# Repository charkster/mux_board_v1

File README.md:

# mux_board_v1
Custom PCB with ItsyBitsy M0 Express controlling **FOUR ADG1606BRUZ 16 input muxes!**

**--> UPDATED design available: [mux_board_v5](https://github.com/charkster/mux_board_v5) <--**

Check-out my **PDF** [schematic](https://github.com/charkster/mux_board_v1/blob/main/kicad/mux_board_v1_sch_plot.pdf) !!

This board is super-easy to order from Oshpark. Just upload kicad/mux_board_v1.kicad_pcb and pay $31 for 3 boards (including shipping).
The ItsyBitsy M0 Express board was selected as (1) I am very familar with the samd21, (2) it has enought gpios to control all the muxes and (3) it is $12 and almost always in-stock. The ItsyBitsy board can be programmed by just double-clicking the reset button and drag-n-drop the itsybitsy_m0-usbtmc_mux_board.uf2 file.

**Welcome to the fricken future people...** drag-n-drop the kicad_pcb file to order the board, and drag-n-drop the uf2 file to program the MCU! Sorry, nothing I can do about the soldering.

Mux outputs are on the 1757268 connector, which is a Phoenix Contact connector. This connector can be omitted and posts can be put in the holes.

Dual channel opamp and muxes working great, but the level-shifter schematic is incorrect (don't populate the NVT2008 part). The NVT2008 needs to have high value resistors connect to the VREFB and EN inputs (unlike the TI TXS01018E).

What am I planning to do with this board? I need to connect two Keithley 2460 SMUs to my ASIC board to support bench trimming. I thought this would be a cool new lab instrument. The VDD PIN can be driven by the USB's 5V or externally up to 16V (mux inputs should be less than VDD).

Here are the SCPI commands which can be used:

**MUX1:EN 1** # enable MUX1, a zero will disable the mux

**MUX1:SEL 1** # select S1 input, values 1 through 16 are valid

**MUX1:EN?** # this query returns the state of MUX1

**MUX1:SEL?** # this query returns the presently selected input

**SOURC1:VOLT:LEV 2.2** # drive 2.2V from DAC

**SOURC1:VOLT:LEV?** # this query returns the DAC level

***RST** # disables all MUX enables and sets DAC to 0V

***IDN?** # returns valid commands and this URL

The tinyusb_usbtmc files are modifications of https://github.com/hathach/tinyusb source files.

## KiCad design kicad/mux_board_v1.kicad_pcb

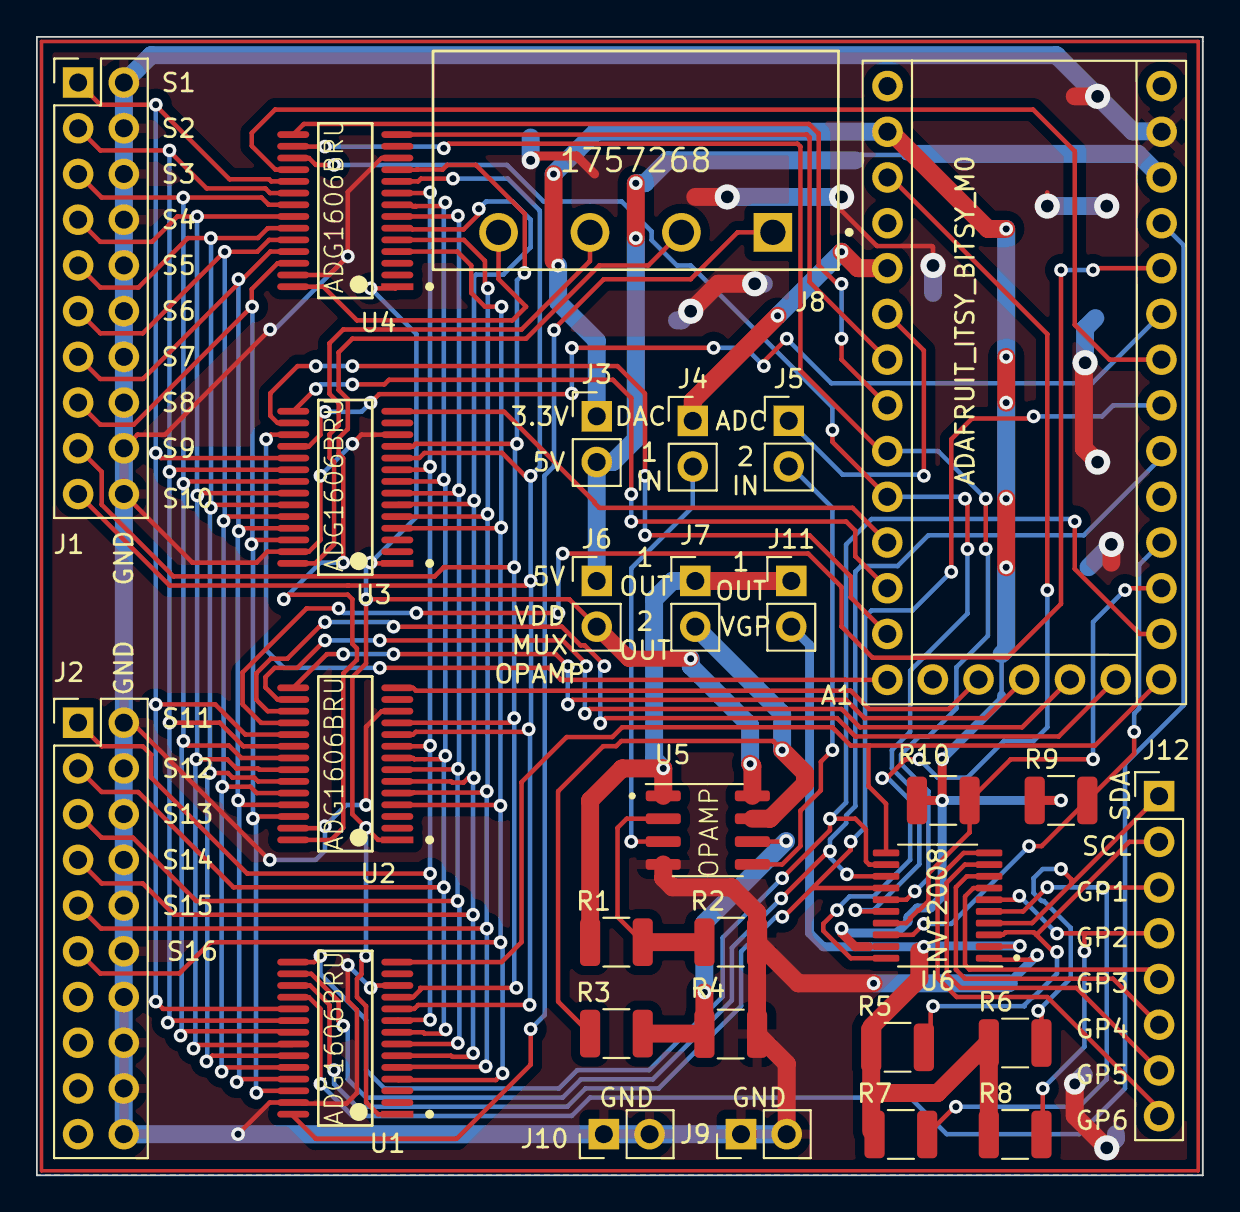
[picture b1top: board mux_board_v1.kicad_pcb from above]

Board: 2 copper layers, 64.8 x 63.2 mm, 29 parts (0 on the bottom side), 64 nets.

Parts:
A1: ADAFRUIT_ITSY_BITSY_M0; Adafruit_Itsy_Bitsy_M0
J1, J2: Conn_02x10_Odd_Even; PinHeader_2x10_P2.54mm_Vertical
J3, J4, J5, J6, J7, J9, J10, J11: Conn_01x02_Male; PinHeader_1x02_P2.54mm_Vertical
J8: 1757268; Phoenix_Contact-1757268-0
J12: Conn_01x08_Male; PinHeader_1x08_P2.54mm_Vertical
R1, R3: 10k; R_1210_3225Metric
R2, R4: 5k; R_1210_3225Metric
R5, R6, R7, R8, R9, R10: 1k; R_1210_3225Metric
U1, U2, U3, U4: ADG1606BRU; Analog_Devices-RU-28-0-0-IPC_A
U5: OPAMP; SOIC-8-1EP_3.9x4.9mm_P1.27mm_EP2.29x3mm
U6: NVT2008; TSSOP-20_4.4x6.5mm_P0.65mm

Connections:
+3V3: A1.32 (3V3), J3.1, R9.1, R10.1, U6.19 (VREFB)
+5V: A1.3 (VUSB), J3.2, J6.1
/1IN-: R1.2, R2.1, U5.2 (1IN-)
/1OUT: J7.1, J11.1, R1.1, U5.1 (1OUT)
/2OUT: J7.2, R3.1, U5.7 (2OUT)
/ADC: A1.28 (A1), J5.1
/DAC: A1.29 (A0), J4.1
/GPIO1: J12.3, R7.2, U6.5 (A3)
/GPIO2: J12.4, R8.2, U6.6 (A4)
/GPIO3: J12.5, U6.7 (A5)
/GPIO4: J12.6, U6.8 (A6)
/GPIO5: J12.7, U6.9 (A7)
/GPIO6: J12.8, U6.10 (A8)
/LS_EN: A1.31 (AVREF), U6.20 (EN)
/MUX1_EN: A1.4 (D13), U1.18 (EN)
/MUX1_OUT: J8.1, U1.28 (D)
/MUX1_SEL0: A1.8 (D9), U1.17 (A0), U6.14 (B5)
/MUX1_SEL1: A1.9 (D7), U1.16 (A1), U6.13 (B6)
/MUX1_SEL2: A1.13 (D1), U1.15 (A2), U6.12 (B7)
/MUX1_SEL3: A1.14 (D0), U1.14 (A3), U6.11 (B8)
/MUX2_EN: A1.5 (D12), U2.18 (EN)
/MUX2_OUT: J8.2, U2.28 (D)
/MUX2_SEL0: A1.15 (D4), U2.17 (A0)
/MUX2_SEL1: A1.16 (D3), U2.16 (A1)
/MUX2_SEL2: A1.17 (SWCLK), U2.15 (A2)
/MUX2_SEL3: A1.18 (SWDIO), U2.14 (A3)
/MUX3_EN: A1.6 (D11), U3.18 (EN)
/MUX3_OUT: J8.3, U3.28 (D)
/MUX3_SEL0: A1.20 (D2), U3.17 (A0)
/MUX3_SEL1: A1.21 (MISO), U3.16 (A1)
/MUX3_SEL2: A1.22 (MOSI), U3.15 (A2)
/MUX3_SEL3: A1.23 (SCK), U3.14 (A3)
/MUX4_EN: A1.7 (D10), U4.18 (EN)
/MUX4_OUT: J8.4, U4.28 (D)
/MUX4_SEL0: A1.24 (A5), U4.17 (A0), U6.16 (B3)
/MUX4_SEL1: A1.25 (A4), U4.16 (A1), U6.15 (B4)
/MUX4_SEL2: A1.26 (A3), U4.15 (A2)
/MUX4_SEL3: A1.27 (A2), U4.14 (A3)
/S1: J1.1, U1.19 (S1), U2.19 (S1), U3.19 (S1), U4.19 (S1)
/S2: J1.3, U1.20 (S2), U2.20 (S2), U3.20 (S2), U4.20 (S2)
/S3: J1.5, U1.21 (S3), U2.21 (S3), U3.21 (S3), U4.21 (S3)
/S4: J1.7, U1.22 (S4), U2.22 (S4), U3.22 (S4), U4.22 (S4)
/S5: J1.9, U1.23 (S5), U2.23 (S5), U3.23 (S5), U4.23 (S5)
/S6: J1.11, U1.24 (S6), U2.24 (S6), U3.24 (S6), U4.24 (S6)
/S7: J1.13, U1.25 (S7), U2.25 (S7), U3.25 (S7), U4.25 (S7)
/S8: J1.15, U1.26 (S8), U2.26 (S8), U3.26 (S8), U4.26 (S8)
/S9: J1.17, U1.11 (S9), U2.11 (S9), U3.11 (S9), U4.11 (S9)
/S10: J1.19, U1.10 (S10), U2.10 (S10), U3.10 (S10), U4.10 (S10)
/S11: J2.1, U1.9 (S11), U2.9 (S11), U3.9 (S11), U4.9 (S11)
/S12: J2.3, U1.8 (S12), U2.8 (S12), U3.8 (S12), U4.8 (S12)
/S13: J2.5, U1.7 (S13), U2.7 (S13), U3.7 (S13), U4.7 (S13)
/S14: J2.7, U1.6 (S14), U2.6 (S14), U3.6 (S14), U4.6 (S14)
/S15: J2.9, U1.5 (S15), U2.5 (S15), U3.5 (S15), U4.5 (S15)
/S16: J2.11, U1.4 (S16), U2.4 (S16), U3.4 (S16), U4.4 (S16)
/SCL: J12.2, R5.2, U6.3 (A1)
/SCL_3V3: A1.11 (SCL), R9.2, U6.18 (B1)
/SDA: J12.1, R6.2, U6.4 (A2)
/SDA_3V3: A1.12 (SDA), R10.2, U6.17 (B2)
/VDD: J6.2, U1.1 (VDD), U2.1 (VDD), U3.1 (VDD), U4.1 (VDD), U5.8 (VDD)
/VREFA: J11.2, R5.1, R6.1, R7.1, R8.1, U6.2 (VREFA)
GND: A1.2 (GND), J1.2, J1.4, J1.6, J1.8, J1.10, J1.12, J1.14, J1.16, J1.18, J1.20, J2.2, J2.4, J2.6, J2.8, J2.10, J2.12, J2.14, J2.16, J2.18, J2.20, J9.1, J9.2, J10.1, J10.2, R2.2, R4.2, U1.12 (GND), U1.27 (VSS), U2.12 (GND), U2.27 (VSS), U3.12 (GND), U3.27 (VSS), U4.12 (GND), U4.27 (VSS), U5.4 (GND), U6.1 (GND)
unnamed: J4.2, U5.3 (1IN+)
unnamed: J5.2, U5.5 (2IN+)
unnamed: R3.2, R4.1, U5.6 (2IN-)

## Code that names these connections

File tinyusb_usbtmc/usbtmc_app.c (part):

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#define DOTSTAR_CLK     PORT_PA00
#define DAC_PORT        PORT_PA02
#define ADC_PORT        PORT_PB08 // PORT B
#define MUX1_EN_PORT    PORT_PA17
#define MUX1_EN_PIN      PIN_PA17
#define MUX1_S0_PORT    PORT_PA07
#define MUX1_S0_PIN      PIN_PA07
#define MUX1_S1_PORT    PORT_PA21
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#define MUX1_S2_PIN      PIN_PA10
#define MUX1_S3_PORT    PORT_PA11
#define MUX1_S3_PIN      PIN_PA11
#define MUX2_EN_PORT    PORT_PA19
#define MUX2_EN_PIN      PIN_PA19
#define MUX2_S0_PORT    PORT_PA08
#define MUX2_S0_PIN      PIN_PA08
#define MUX2_S1_PORT    PORT_PA09
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#define MUX2_S2_PIN      PIN_PA30
#define MUX2_S3_PORT    PORT_PA31
#define MUX2_S3_PIN      PIN_PA31
#define MUX3_EN_PORT    PORT_PA16
#define MUX3_EN_PIN      PIN_PA16
#define MUX3_S0_PORT    PORT_PA14
#define MUX3_S0_PIN      PIN_PA14
#define MUX3_S1_PORT    PORT_PA12
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#define MUX3_S2_PIN      PIN_PB10
#define MUX3_S3_PORT    PORT_PB11 // PORT B
#define MUX3_S3_PIN      PIN_PB11
#define MUX4_EN_PORT    PORT_PA18
#define MUX4_EN_PIN      PIN_PA18
#define MUX4_S0_PORT    PORT_PB02 // PORT B
#define MUX4_S0_PIN      PIN_PB02
#define MUX4_S1_PORT    PORT_PA05
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#define MUX4_S2_PIN      PIN_PA04
#define MUX4_S3_PORT    PORT_PB09 // PORT B
#define MUX4_S3_PIN      PIN_PB09
#define LS_EN_PORT      PORT_PA03
#define LS_EN_PIN        PIN_PA03
#define GPIO1_PORT      PORT_PB02 // PORT B, same as MUX4_S0_PORT
#define GPIO1_PIN        PIN_PB02
#define GPIO2_PORT      PORT_PA05 //         same as MUX4_S1_PORT
#define GPIO2_PIN        PIN_PA05
#define GPIO3_PORT      PORT_PA04 //         same as MUX4_S2_PORT
#define GPIO3_PIN        PIN_PA04
#define GPIO4_PORT      PORT_PB09 // PORT B, same as MUX4_S3_PORT
#define GPIO4_PIN        PIN_PB09
#define GPIO5_PORT      PORT_PA14 //         same as MUX3_S0_PORT
#define GPIO5_PIN        PIN_PA14
#define GPIO6_PORT      PORT_PA12 //         same as MUX3_S1_PORT
#define GPIO6_PIN        PIN_PA12
#define SDA_PORT        PORT_PA22
#define SCL_PORT        PORT_PB11  // PORT B
#define DAC_MAX_VALUE   1024 // 10bit value
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#define MUX4_SEL_QUERY  "mux4:sel?"        // MUX4:SEL
#define MUX4_EN_CMD     "mux4:en "         // MUX4:ENable
#define MUX4_EN_QUERY   "mux4:en?"         // MUX4:ENable
#define GPIO1_LEV_CMD    "gpio1:lev "      // GPIO1:LEVel
#define GPIO1_LEV_QUERY  "gpio1:lev?"      // GPIO1:LEVel
#define GPIO1_DIR_CMD    "gpio1:dir "      // GPIO1:DIRection
#define GPIO1_DIR_QUERY  "gpio1:dir?"      // GPIO1:DIRection
#define GPIO2_LEV_CMD    "gpio2:lev "      // GPIO2:LEVel
#define GPIO2_LEV_QUERY  "gpio2:lev?"      // GPIO2:LEVel
#define GPIO2_DIR_CMD    "gpio2:dir "      // GPIO2:DIRection
#define GPIO2_DIR_QUERY  "gpio2:dir?"      // GPIO2:DIRection
#define GPIO3_LEV_CMD    "gpio3:lev "      // GPIO3:LEVel
#define GPIO3_LEV_QUERY  "gpio3:lev?"      // GPIO3:LEVel
#define GPIO3_DIR_CMD    "gpio3:dir "      // GPIO3:DIRection
#define GPIO3_DIR_QUERY  "gpio3:dir?"      // GPIO3:DIRection
#define GPIO4_LEV_CMD    "gpio4:lev "      // GPIO4:LEVel
#define GPIO4_LEV_QUERY  "gpio4:lev?"      // GPIO4:LEVel
#define GPIO4_DIR_CMD    "gpio4:dir "      // GPIO4:DIRection
#define GPIO4_DIR_QUERY  "gpio4:dir?"      // GPIO4:DIRection
#define GPIO5_LEV_CMD    "gpio5:lev "      // GPIO5:LEVel
#define GPIO5_LEV_QUERY  "gpio5:lev?"      // GPIO5:LEVel
#define GPIO5_DIR_CMD    "gpio5:dir "      // GPIO5:DIRection
#define GPIO5_DIR_QUERY  "gpio5:dir?"      // GPIO5:DIRection
#define GPIO6_LEV_CMD    "gpio6:lev "      // GPIO6:LEVel
#define GPIO6_LEV_QUERY  "gpio6:lev?"      // GPIO6:LEVel
#define GPIO6_DIR_CMD    "gpio6:dir "      // GPIO6:DIRection
#define GPIO6_DIR_QUERY  "gpio6:dir?"      // GPIO6:DIRection
#define END_RESPONSE    "\n"               // USB488

#include <strings.h>
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  {
    rst_cmd = true;
    DAC->DATA.reg = 0x0000;                  // clear DAC value
    PORT->Group[MUX1_EN_PIN/32].DIRSET.reg = MUX1_EN_PORT; // mux enable as output
    PORT->Group[MUX1_EN_PIN/32].OUTCLR.reg = MUX1_EN_PORT; // mux_enable drive low value
    PORT->Group[MUX2_EN_PIN/32].DIRSET.reg = MUX2_EN_PORT; // mux enable as output
    PORT->Group[MUX2_EN_PIN/32].OUTCLR.reg = MUX2_EN_PORT; // mux_enable drive low value
    PORT->Group[MUX3_EN_PIN/32].DIRSET.reg = MUX3_EN_PORT; // mux enable as output
    PORT->Group[MUX3_EN_PIN/32].OUTCLR.reg = MUX3_EN_PORT; // mux_enable drive low value
    PORT->Group[MUX4_EN_PIN/32].DIRSET.reg = MUX4_EN_PORT; // mux enable as output
    PORT->Group[MUX4_EN_PIN/32].OUTCLR.reg = MUX4_EN_PORT; // mux_enable drive low value
  }
  else if (transfer_complete && (len >=16) && !strncasecmp(DAC_CMD,data,16))
  {
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  {
    mux_en_cmd  = true;
    MUX_EN_PORT = MUX1_EN_PORT;
    MUX_EN_PIN  = MUX1_EN_PIN;
    PORT->Group[0].DIRSET.reg = MUX1_EN_PORT | MUX1_S3_PORT | MUX1_S2_PORT | MUX1_S1_PORT | MUX1_S0_PORT; // mux enable and sel as outputs
  }
  else if (transfer_complete && (len >= 8) && !strncasecmp(MUX2_EN_CMD,data,8))
  {
    mux_en_cmd  = true;
    MUX_EN_PORT = MUX2_EN_PORT;
    MUX_EN_PIN  = MUX2_EN_PIN;
    PORT->Group[0].DIRSET.reg = MUX2_EN_PORT | MUX2_S3_PORT | MUX2_S2_PORT | MUX2_S1_PORT | MUX2_S0_PORT; // mux enable and sel as outputs
  }
  else if (transfer_complete && (len >= 8) && !strncasecmp(MUX3_EN_CMD,data,8))
  {
    mux_en_cmd  = true;
    MUX_EN_PORT = MUX3_EN_PORT;
    MUX_EN_PIN  = MUX3_EN_PIN;
    PORT->Group[0].DIRSET.reg = MUX3_EN_PORT | MUX3_S3_PORT | MUX3_S2_PORT | MUX3_S1_PORT | MUX3_S0_PORT; // mux enable and sel as outputs
  }
  else if (transfer_complete && (len >= 8) && !strncasecmp(MUX4_EN_CMD,data,8))
  {
    mux_en_cmd  = true;
    MUX_EN_PORT = MUX4_EN_PORT;
    MUX_EN_PIN  = MUX4_EN_PIN;
    PORT->Group[0].DIRSET.reg = MUX4_EN_PORT | MUX4_S3_PORT | MUX4_S2_PORT | MUX4_S1_PORT | MUX4_S0_PORT; // mux enable and sel as outputs
  }
  else if (transfer_complete && (len >= 8) && !strncasecmp(MUX1_EN_QUERY,data,8))
  {
    mux_en_query = true;
    MUX_EN_PORT  = MUX1_EN_PORT;
    MUX_EN_PIN   = MUX1_EN_PIN;
  }
  else if (transfer_complete && (len >= 8) && !strncasecmp(MUX2_EN_QUERY,data,8))
  {
    mux_en_query = true;
    MUX_EN_PORT  = MUX2_EN_PORT;
    MUX_EN_PIN   = MUX2_EN_PIN;
  }
  else if (transfer_complete && (len >= 8) && !strncasecmp(MUX3_EN_QUERY,data,8))
  {
    mux_en_query = true;
    MUX_EN_PORT  = MUX3_EN_PORT;
    MUX_EN_PIN   = MUX3_EN_PIN;
  }
  else if (transfer_complete && (len >= 8) && !strncasecmp(MUX4_EN_QUERY,data,8))
  {
    mux_en_query = true;
    MUX_EN_PORT  = MUX4_EN_PORT;
    MUX_EN_PIN   = MUX4_EN_PIN;
  }
  else if (transfer_complete && (len >= 9) && !strncasecmp(MUX1_SEL_CMD,data,9))
  {
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    MUX_S1_PIN   = MUX3_S1_PIN;
    MUX_S2_PIN   = MUX3_S2_PIN;
    MUX_S3_PIN   = MUX3_S3_PIN;
    PORT->Group[(LS_EN_PIN/32)].OUTCLR.reg = LS_EN_PORT;   // disable the level-shifters
  }
  else if (transfer_complete && (len >= 9) && !strncasecmp(MUX4_SEL_CMD,data,9))
  {
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    MUX_S1_PIN   = MUX4_S1_PIN;
    MUX_S2_PIN   = MUX4_S2_PIN;
    MUX_S3_PIN   = MUX4_S3_PIN;
    PORT->Group[(LS_EN_PIN/32)].OUTCLR.reg = LS_EN_PORT;   // disable the level-shifters
  }
  else if (transfer_complete && (len >= 9) && !strncasecmp(MUX1_SEL_QUERY,data,9))
  {
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  else if (transfer_complete && (len >= 10) && !strncasecmp(GPIO1_LEV_CMD,data,10))
  {
    gpio_lev_cmd = true;
    GPIO_PORT    = GPIO1_PORT;
    GPIO_PIN     = GPIO1_PIN;
  }
  else if (transfer_complete && (len >= 10) && !strncasecmp(GPIO2_LEV_CMD,data,10))
  {
    gpio_lev_cmd = true;
    GPIO_PORT    = GPIO2_PORT;
    GPIO_PIN     = GPIO2_PIN;
  }
  else if (transfer_complete && (len >= 10) && !strncasecmp(GPIO3_LEV_CMD,data,10))
  {
    gpio_lev_cmd = true;
    GPIO_PORT    = GPIO3_PORT;
    GPIO_PIN     = GPIO3_PIN;
  }
  else if (transfer_complete && (len >= 10) && !strncasecmp(GPIO4_LEV_CMD,data,10))
  {
    gpio_lev_cmd = true;
    GPIO_PORT    = GPIO4_PORT;
    GPIO_PIN     = GPIO4_PIN;
  }
  else if (transfer_complete && (len >= 10) && !strncasecmp(GPIO5_LEV_CMD,data,10))
  {
    gpio_lev_cmd = true;
    GPIO_PORT    = GPIO5_PORT;
    GPIO_PIN     = GPIO5_PIN;
  }
  else if (transfer_complete && (len >= 10) && !strncasecmp(GPIO6_LEV_CMD,data,10))
  {
    gpio_lev_cmd = true;
    GPIO_PORT    = GPIO6_PORT;
    GPIO_PIN     = GPIO6_PIN;
  }
  else if (transfer_complete && (len >= 10) && !strncasecmp(GPIO1_LEV_QUERY,data,10))
  {
    gpio_lev_query = true;
    GPIO_PORT      = GPIO1_PORT;
    GPIO_PIN       = GPIO1_PIN;
  }
  else if (transfer_complete && (len >= 10) && !strncasecmp(GPIO2_LEV_QUERY,data,10))
  {
    gpio_lev_query = true;
    GPIO_PORT      = GPIO2_PORT;
    GPIO_PIN       = GPIO2_PIN;
  }
  else if (transfer_complete && (len >= 10) && !strncasecmp(GPIO3_LEV_QUERY,data,10))
  {
    gpio_lev_query = true;
    GPIO_PORT      = GPIO3_PORT;
    GPIO_PIN       = GPIO3_PIN;
  }
  else if (transfer_complete && (len >= 10) && !strncasecmp(GPIO4_LEV_QUERY,data,10))
  {
    gpio_lev_query = true;
    GPIO_PORT      = GPIO4_PORT;
    GPIO_PIN       = GPIO4_PIN;
  }
  else if (transfer_complete && (len >= 10) && !strncasecmp(GPIO5_LEV_QUERY,data,10))
  {
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
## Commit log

2022-10-22 Create LICENSE
2023-05-04 Update README.md
    added link to mux_board_v5

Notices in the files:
tinyusb_usbtmc/usbtmc_app.c:
The MIT License (MIT)
Copyright (c) 2019 Nathan Conrad
kicad/mux_board_v1.kicad_pcb:
creativecommons.org/licenses/by/4.0
License: CC BY 4.0
